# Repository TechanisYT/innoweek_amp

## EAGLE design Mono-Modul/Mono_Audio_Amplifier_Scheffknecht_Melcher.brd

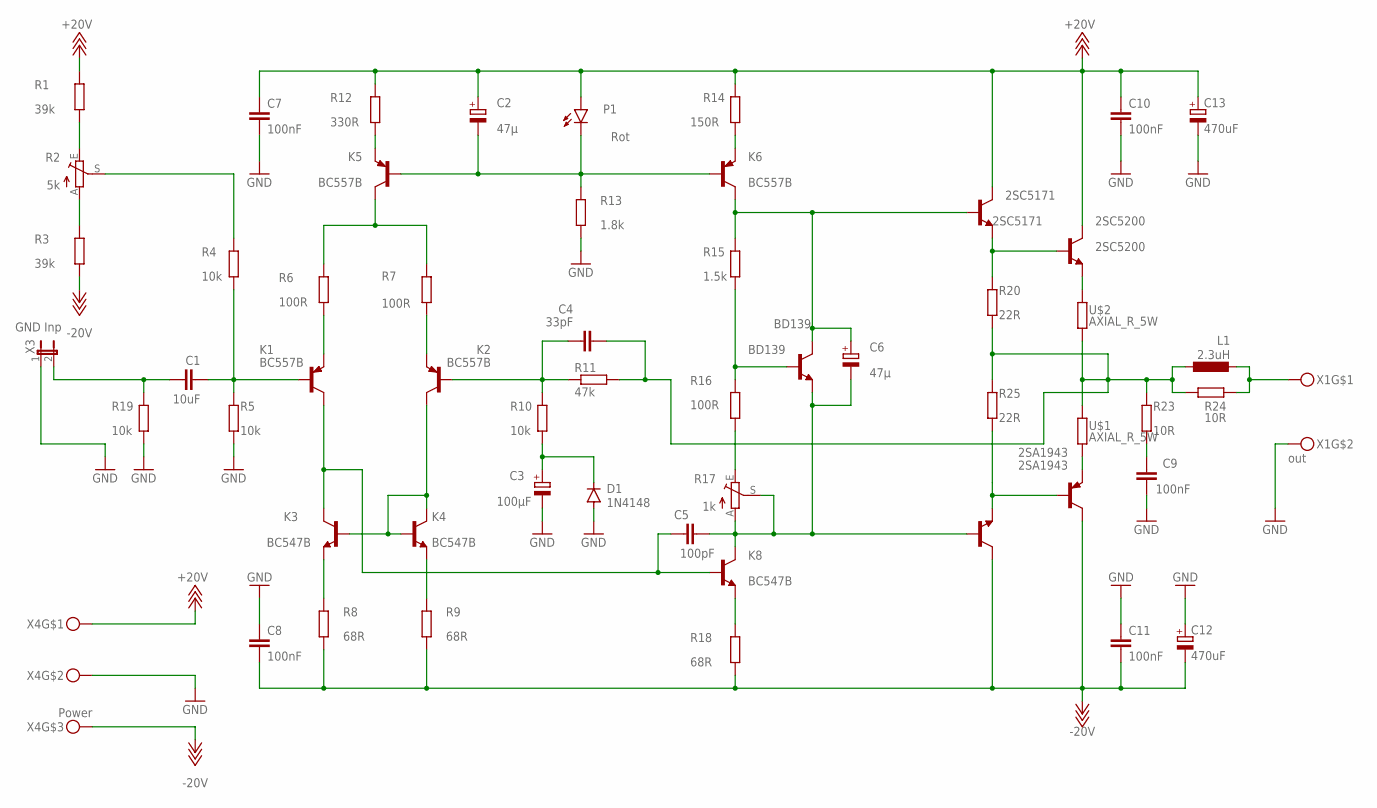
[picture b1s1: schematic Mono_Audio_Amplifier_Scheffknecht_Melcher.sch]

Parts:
2SA1930: 2SA1930; TO220BV
2SA1943: 2SA1943; TO264
2SC5171: 2SC5171; TO220BV
2SC5200: 2SC5200; TO264
BD139: BD139; TO126V
C1: 10uF; C0805
C2, C6: 47µ; E2,5-6
C3: 100µF; E2,5-7
C4: 33pF; C0805
C5: 100pF; C0805
C7, C8, C9, C10, C11: 100nF; C0805
C12, C13: 470uF; E3,5-8
D1: 1N4148; DO35-7
K1, K2, K5, K6: BC557B; TO92-EBC
K3, K4, K8: BC547B; TO92-CBE
L1: 2.3uH; TJ3-U2
P1: Rot; LED5MM
R1, R3: 39k; R0805
R2: 5k; S64W
R4, R5, R10, R19: 10k; R0805
R6, R7, R16: 100R; R0805
R8, R9, R18: 68R; R0805
R11: 47k; R0805
R12: 330R; R0805
R13: 1.8k; R0805
R14: 150R; R0805
R15: 1.5k; R0805
R17: 1k; S64W
R20, R25: 22R; R0805
R23, R24: 10R; R0805
U$1, U$2: AXIAL_R_5W; AXIAL_RESISTOR
X1: out; MKDS3/2_5,08
X3: GND Inp; JMP2
X4: Power; MKDS3/3_5,08

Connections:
+18V: 2SC5171.2 (C), 2SC5200.2 (C), C2.+, C7.1, C10.1, C13.+, P1.A, R1.1, R12.1, R14.1, X4.P$1
-18V: 2SA1930.2 (C), 2SA1943.2 (C), C8.2, C11.2, C12.-, R3.2, R8.2, R9.2, R18.2, X4.P$3
AUX_IN: C1.2, K1.B, R4.2, R5.1
GND: C3.-, C7.2, C8.1, C9.1, C10.2, C11.1, C12.+, C13.-, D1.A, R5.2, R13.2, R19.2, X1.P$2, X3.1, X4.P$2
unnamed: 2SC5200.3 (E), U$2.P$2 (2)
unnamed: 2SC5171.3 (E), 2SC5200.1 (B), R20.2
unnamed: 2SA1943.3 (E), U$1.P$1 (1)
unnamed: C4.2, L1.1, R11.2, R20.1, R23.2, R24.2, R25.2, U$1.P$2 (2), U$2.P$1 (1)
unnamed: C5.1, K1.C, K3.C, K8.B
unnamed: R16.2, R17.E
unnamed: BD139.3 (B), R15.2, R16.1
unnamed: 2SA1930.1 (B), BD139.1 (E), C5.2, C6.-, K8.C, R17.A, R17.S
unnamed: 2SC5171.1 (B), BD139.2 (C), C6.+, K6.C, R15.1
unnamed: K8.E, R18.1
unnamed: K6.E, R14.2
unnamed: K5.C, R6.1, R7.1
unnamed: K5.E, R12.2
unnamed: C4.1, K2.B, R10.1, R11.1
unnamed: K4.E, R9.1
unnamed: C2.-, K5.B, K6.B, P1.K (C), R13.1
unnamed: K1.E, R6.2
unnamed: K3.E, R8.1
unnamed: K2.E, R7.2
unnamed: K2.C, K3.B, K4.B, K4.C
unnamed: C3.+, D1.C, R10.2
unnamed: C9.2, R23.1
unnamed: C1.1, R19.1, X3.2
unnamed: R1.2, R2.E
unnamed: 2SA1930.3 (E), 2SA1943.1 (B), R25.1
unnamed: R2.S, R4.1
unnamed: R2.A, R3.1
unnamed: L1.2, R24.1, X1.P$1

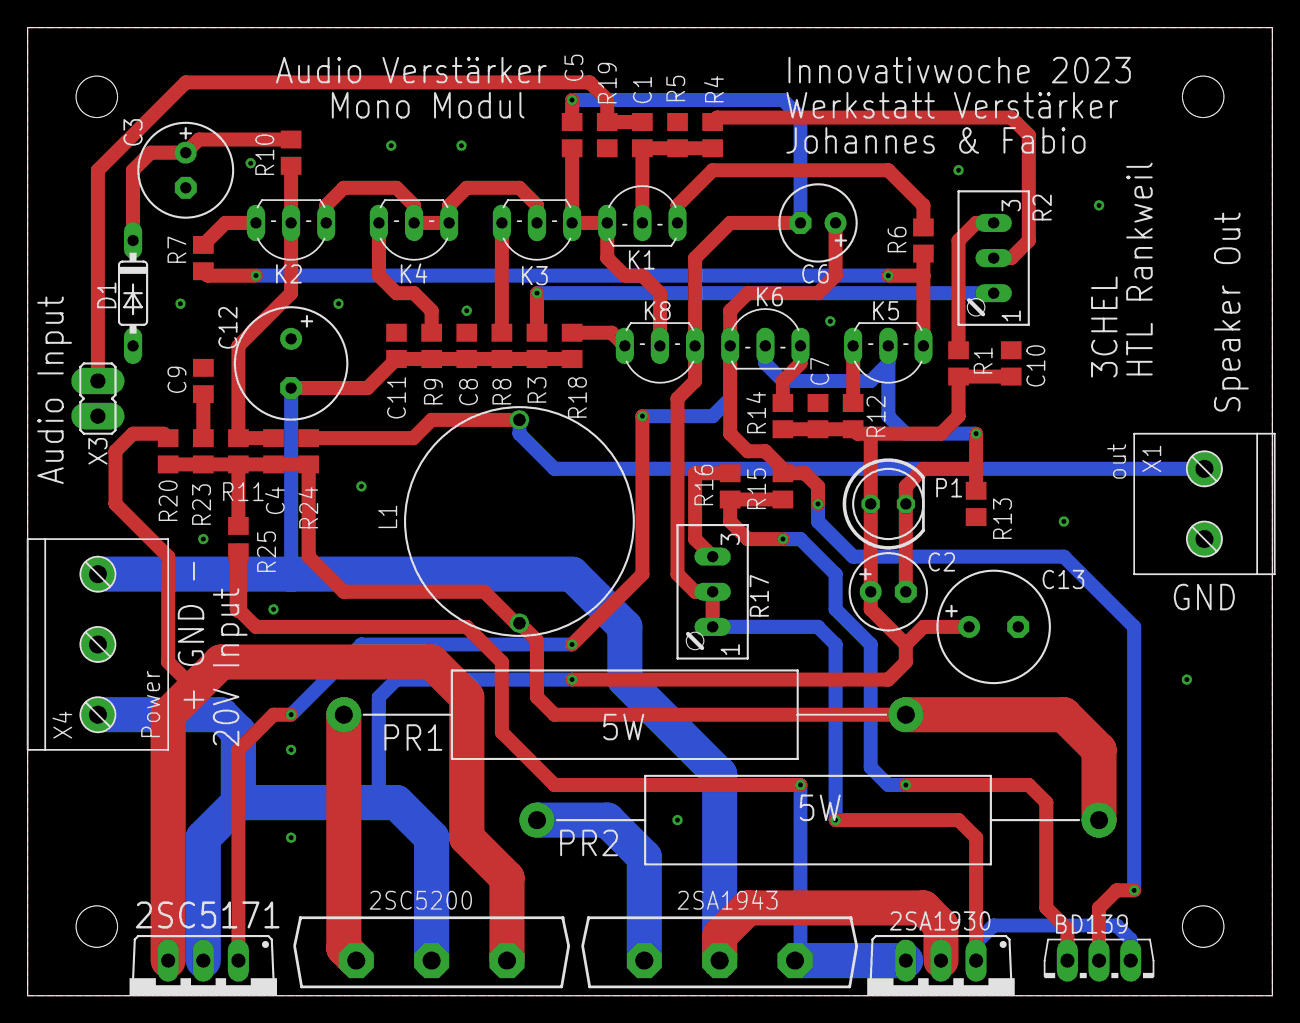
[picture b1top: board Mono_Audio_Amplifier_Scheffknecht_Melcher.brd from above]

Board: 2 copper layers, 90.0 x 70.0 mm, 56 parts (0 on the bottom side), 32 nets.

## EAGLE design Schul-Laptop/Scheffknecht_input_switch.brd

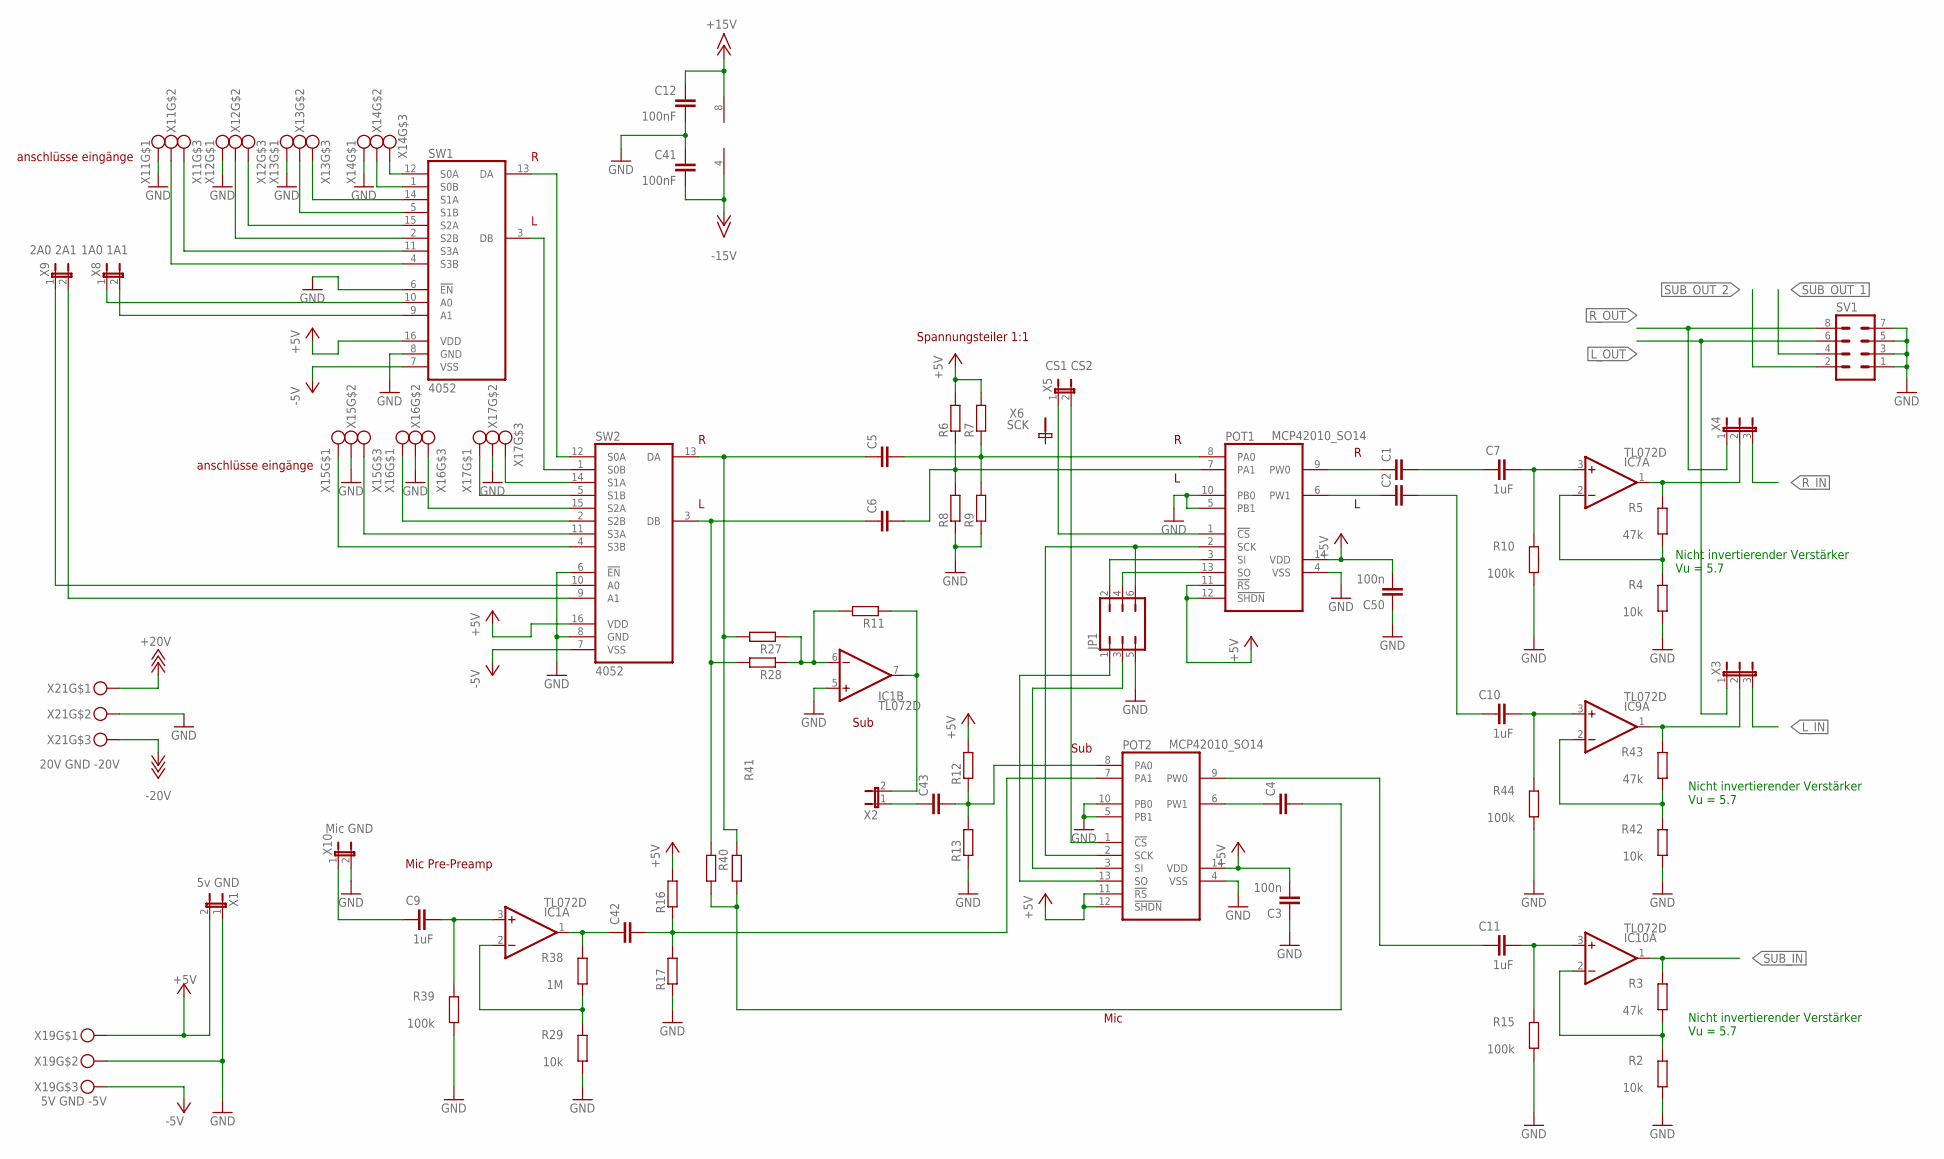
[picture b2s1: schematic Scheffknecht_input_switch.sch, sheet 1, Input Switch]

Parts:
C1, C2, C4, C5, C6, C42, C43: C-EUC0805; C0805
C3, C50: 100n; C0805
C7, C9, C10, C11: 1uF; C025-025X050
C12, C41: 100nF; C0805
FRAME1: HTL-A3-H; HTL-LEER
IC1, IC7, IC9, IC10: TL072D; SO08
JP1: JP3Q
POT1, POT2: MCP42010_SO14; SO14
R2, R4, R29, R42: 10k; M0805
R3, R5, R43: 47k; M0805
R6, R7, R8, R9, R11, R12, R13, R16, R17, R27, R28, R40, R41: R-EU_M0805; M0805
R10, R15, R39, R44: 100k; M0805
R38: 1M; M0805
SV1: MA04-2
SW1, SW2: 4052; SO-16
X1: 5v GND; JMP2
X2: JMP2
X3, X4: JMP3
X5: CS1 CS2; JMP2
X6: SCK; PIN1
X8: 1A0 1A1; JMP2
X9: 2A0 2A1; JMP2
X10: Mic GND; JMP2
X11, X12, X13, X14, X15, X16, X17: MKDS3/3_5,08
X19: 5V GND -5V; MKDS3/3_5,08
X21: 20V GND -20V; MKDS3/3_5,08

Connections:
+5V: C3.2, C50.2, POT1.11 (!RS), POT1.12 (!SHDN), POT1.14 (VDD), POT2.11 (!RS), POT2.12 (!SHDN), POT2.14 (VDD), R6.2, R7.2, R12.2, R16.2, SW1.16 (VDD), SW2.16 (VDD), X1.2, X19.P$1; also elsewhere on the board
+15V: C12.1, IC1.8 (V+); also elsewhere on the board
+18V: X21.P$1; also elsewhere on the board
-5V: SW1.7 (VSS), SW2.7 (VSS), X19.P$3; also elsewhere on the board
-15V: C41.2, IC1.4 (V-); also elsewhere on the board
-18V: X21.P$3; also elsewhere on the board
GND: C3.1, C12.2, C41.1, C50.1, IC1.5 (+IN), JP1.5, POT1.4 (VSS), POT1.5 (PB1), POT1.10 (PB0), POT2.4 (VSS), POT2.5 (PB1), POT2.10 (PB0), R2.1, R4.1, R8.1, R9.1, R10.1, R13.1, R15.1, R17.1, R29.1, R39.1, R42.1, R44.1, SV1.1, SV1.3, SV1.5, SV1.7, SW1.6 (!EN), SW1.8 (GND), SW2.6 (!EN), SW2.8 (GND), X1.1, X10.2, X11.P$1, X12.P$1, X13.P$1, X14.P$1, X15.P$2, X16.P$2, X17.P$2, X19.P$2, X21.P$2; also elsewhere on the board
L_IN: X3.3; also elsewhere on the board
L_OUT: SV1.6, X3.1; also elsewhere on the board
unnamed: POT2.1 (!CS), X5.2
unnamed: POT1.1 (!CS), X5.1
unnamed: SW1.3 (DB), SW2.1 (S0B)
unnamed: SW1.13 (DA), SW2.12 (S0A)
unnamed: SW1.9 (A1), X8.2
unnamed: SW1.10 (A0), X8.1
unnamed: SW2.9 (A1), X9.2
unnamed: SW2.10 (A0), X9.1
unnamed: C5.2, POT1.8 (PA0), R7.1, R9.2
unnamed: JP1.2, POT1.3 (SI)
unnamed: C7.2, IC7.3 (+IN), R10.2
unnamed: C5.1, R27.2, R41.1, SW2.13 (DA)
unnamed: C6.1, R28.2, R40.1, SW2.3 (DB)
unnamed: C2.2, C10.1
unnamed: C10.2, IC9.3 (+IN), R44.2
unnamed: IC1.6 (-IN), R11.2, R27.1, R28.1
unnamed: IC9.2 (-IN), R42.2, R43.1
unnamed: C1.1, POT1.9 (PW0)
unnamed: C6.2, POT1.7 (PA1), R6.1, R8.2
unnamed: C11.1, POT2.9 (PW0)
unnamed: C1.2, C7.1
unnamed: C11.2, IC10.3 (+IN), R15.2
unnamed: IC10.2 (-IN), R2.2, R3.1
unnamed: JP1.1, POT2.13 (SO)
unnamed: C2.1, POT1.6 (PW1)
unnamed: IC7.2 (-IN), R4.2, R5.1
unnamed: C43.2, POT2.8 (PA0), R12.1, R13.2
unnamed: C9.1, X10.1
unnamed: JP1.4, POT1.13 (SO)
unnamed: JP1.3, POT2.3 (SI)
unnamed: C4.1, POT2.6 (PW1)
unnamed: IC1.7 (OUT), R11.1, X2.2
unnamed: C42.2, POT2.7 (PA1), R16.1, R17.2
unnamed: JP1.6, POT1.2 (SCK), POT2.2 (SCK)
unnamed: SW1.12 (S0A), X14.P$3
unnamed: SW1.1 (S0B), X14.P$2
unnamed: SW1.14 (S1A), X13.P$3
unnamed: SW1.5 (S1B), X13.P$2
unnamed: SW1.15 (S2A), X12.P$3
unnamed: SW1.2 (S2B), X12.P$2
unnamed: SW1.11 (S3A), X11.P$3
unnamed: SW1.4 (S3B), X11.P$2
unnamed: SW2.14 (S1A), X17.P$3
unnamed: SW2.5 (S1B), X17.P$1
unnamed: SW2.15 (S2A), X16.P$3
unnamed: SW2.2 (S2B), X16.P$1
unnamed: SW2.11 (S3A), X15.P$3
unnamed: SW2.4 (S3B), X15.P$1
unnamed: C9.2, IC1.3 (+IN), R39.2
unnamed: IC9.1 (OUT), R43.2, X3.2
unnamed: IC7.1 (OUT), R5.2, X4.2
unnamed: IC1.2 (-IN), R29.2, R38.1
unnamed: C43.1, X2.1
unnamed: C42.1, IC1.1 (OUT), R38.2
unnamed: C4.2, R40.2, R41.2
R_IN: X4.3; also elsewhere on the board
R_OUT: SV1.8, X4.1; also elsewhere on the board
SUB_IN: IC10.1 (OUT), R3.2; also elsewhere on the board
SUB_OUT_1: SV1.4; also elsewhere on the board
SUB_OUT_2: SV1.2; also elsewhere on the board
V+: IC7.8 (V+), IC9.8 (V+), IC10.8 (V+)
V-: IC7.4 (V-), IC9.4 (V-), IC10.4 (V-)

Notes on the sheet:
Spannungsteiler 1:1
Sub
anschlüsse eingänge
Mic Pre-Preamp
Mic
Nicht invertierender Verstärker Vu = 5.7

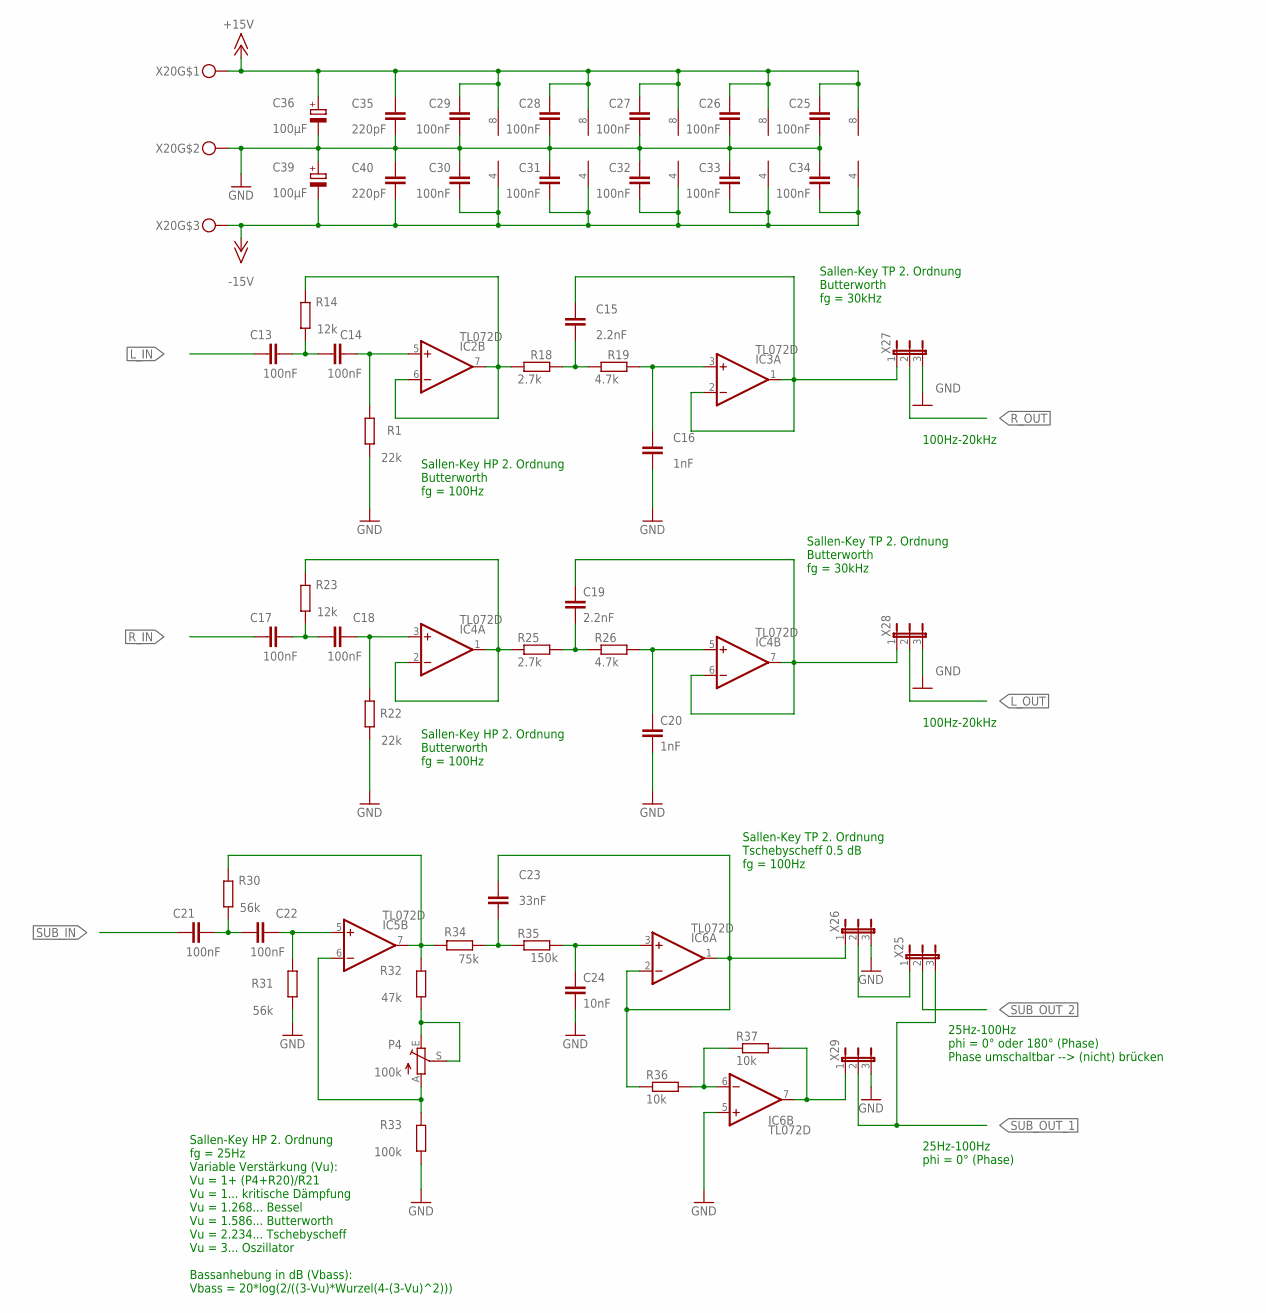
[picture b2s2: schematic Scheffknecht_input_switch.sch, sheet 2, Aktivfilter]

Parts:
C13, C14, C17, C18, C21, C22, C25, C26, C27, C28, C29, C30, C31, C32, C33, C34: 100nF; C0805
C15, C19: 2.2nF; C0805
C16, C20: 1nF; C0805
C23: 33nF; C0805
C24: 10nF; C0805
C35, C40: 220pF; C0805
C36, C39: 100µF; E2,5-6
FRAME2: HTL-A3-H; HTL-LEER
IC2, IC3, IC4, IC5, IC6: TL072D; SO08
P4: 100k; S64W
R1, R22: 22k; M0805
R14, R23: 12k; M0805
R18, R25: 2.7k; M0805
R19, R26: 4.7k; M0805
R30, R31: 56k; M0805
R32: 47k; M0805
R33: 100k; M0805
R34: 75k; M0805
R35: 150k; M0805
R36, R37: 10k; M0805
X20: MKDS3/3_5,08
X25, X26, X27, X28, X29: JMP3

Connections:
+15V: C25.1, C26.1, C27.1, C28.1, C29.1, C35.1, C36.+, IC2.8 (V+), IC3.8 (V+), IC4.8 (V+), IC5.8 (V+), IC6.8 (V+), X20.P$1; also elsewhere on the board
-15V: C30.2, C31.2, C32.2, C33.2, C34.2, C39.-, C40.2, IC2.4 (V-), IC3.4 (V-), IC4.4 (V-), IC5.4 (V-), IC6.4 (V-), X20.P$3; also elsewhere on the board
GND: C16.2, C20.2, C24.2, IC6.5 (+IN), R1.1, R22.1, R31.1, R33.1, X26.3, X27.3, X28.3, X29.3; also elsewhere on the board
GND1: C25.2, C26.2, C27.2, C28.2, C29.2, C30.1, C31.1, C32.1, C33.1, C34.1, C35.2, C36.-, C39.+, C40.1, X20.P$2
L_IN: C13.1; also elsewhere on the board
L_OUT: X28.2; also elsewhere on the board
unnamed: IC2.6 (-IN), IC2.7 (OUT), R14.2, R18.1
unnamed: C14.2, IC2.5 (+IN), R1.2
unnamed: C13.2, C14.1, R14.1
unnamed: C15.2, R18.2, R19.1
unnamed: C16.1, IC3.3 (+IN), R19.2
unnamed: C15.1, IC3.1 (OUT), IC3.2 (-IN), X27.1
unnamed: IC4.1 (OUT), IC4.2 (-IN), R23.2, R25.1
unnamed: C18.2, IC4.3 (+IN), R22.2
unnamed: C17.2, C18.1, R23.1
unnamed: C19.2, R25.2, R26.1
unnamed: C20.1, IC4.5 (+IN), R26.2
unnamed: C19.1, IC4.6 (-IN), IC4.7 (OUT)
unnamed: C21.2, C22.1, R30.1
unnamed: C22.2, IC5.5 (+IN), R31.2
unnamed: IC5.7 (OUT), R30.2, R32.2, R34.2
unnamed: IC5.6 (-IN), P4.A, R33.2
unnamed: P4.E, P4.S, R32.1
unnamed: C24.1, IC6.3 (+IN), R35.2
unnamed: C23.2, R34.1, R35.1
unnamed: IC6.6 (-IN), R36.2, R37.1
unnamed: X25.1, X26.2
R_IN: C17.1; also elsewhere on the board
R_OUT: X27.2; also elsewhere on the board
SUB_IN: C21.1; also elsewhere on the board
SUB_OUT: IC6.7 (OUT), R37.2, X29.1
SUB_OUT-180: C23.1, IC6.1 (OUT), IC6.2 (-IN), R36.1, X26.1
SUB_OUT_1: X25.3, X29.2; also elsewhere on the board
SUB_OUT_2: X25.2; also elsewhere on the board

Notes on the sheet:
100Hz-20kHz
25Hz-100Hz phi = 0° oder 180° (Phase) Phase umschaltbar --> (nicht) brücken
25Hz-100Hz phi = 0° (Phase)
Sallen-Key TP 2. Ordnung Butterworth fg = 30kHz
Sallen-Key HP 2. Ordnung Butterworth fg = 100Hz
Sallen-Key TP 2. Ordnung Tschebyscheff 0.5 dB fg = 100Hz
Sallen-Key HP 2. Ordnung fg = 25Hz Variable Verstärkung (Vu): Vu = 1+ (P4+R20)/R21 Vu = 1... kritische Dämpfung Vu = 1.268... Bessel Vu = 1.586... Butterworth Vu = 2.234... Tschebyscheff Vu = 3... Oszillator Bassanhebung in dB (Vbass): Vbass = 20*log(2/((3-Vu)*Wurzel(4-(3-Vu)^2)))

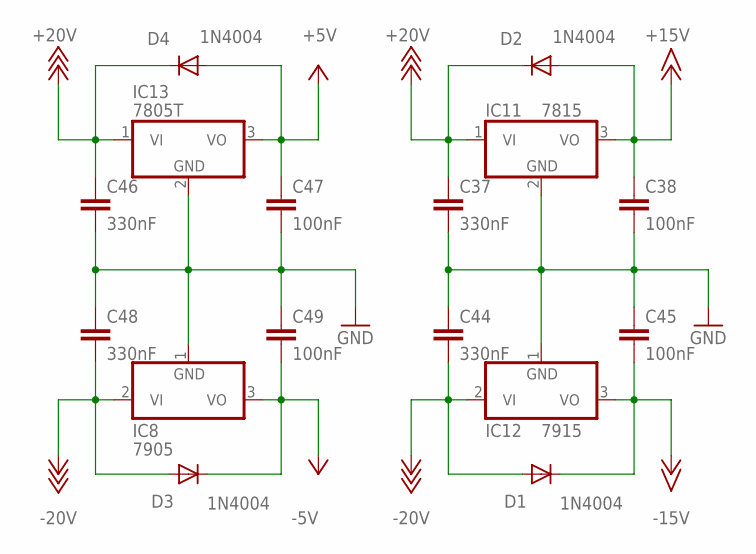
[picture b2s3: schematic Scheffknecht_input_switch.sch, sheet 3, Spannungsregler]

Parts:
C37, C44, C46, C48: 330nF; C0805
C38, C45, C47, C49: 100nF; C0805
D1, D2, D3, D4: 1N4004; DO41-10
FRAME3: HTL-A4-H; HTL-LEER
IC8: 7905; TO220H
IC11: 7815; TO220H
IC12: 7915; TO220H
IC13: 7805T; TO220H

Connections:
+5V: C47.1, D4.A, IC13.3 (VO); also elsewhere on the board
+15V: C38.1, D2.A, IC11.3 (VO); also elsewhere on the board
+18V: C37.1, C46.1, D2.C, D4.C, IC11.1 (VI), IC13.1 (VI); also elsewhere on the board
-5V: C49.2, D3.C, IC8.3 (VO); also elsewhere on the board
-15V: C45.2, D1.C, IC12.3 (VO); also elsewhere on the board
-18V: C44.2, C48.2, D1.A, D3.A, IC8.2 (VI), IC12.2 (VI); also elsewhere on the board
GND: C37.2, C38.2, C44.1, C45.1, C46.2, C47.2, C48.1, C49.1, IC8.1 (GND), IC11.2 (GND), IC12.1 (GND), IC13.2 (GND); also elsewhere on the board

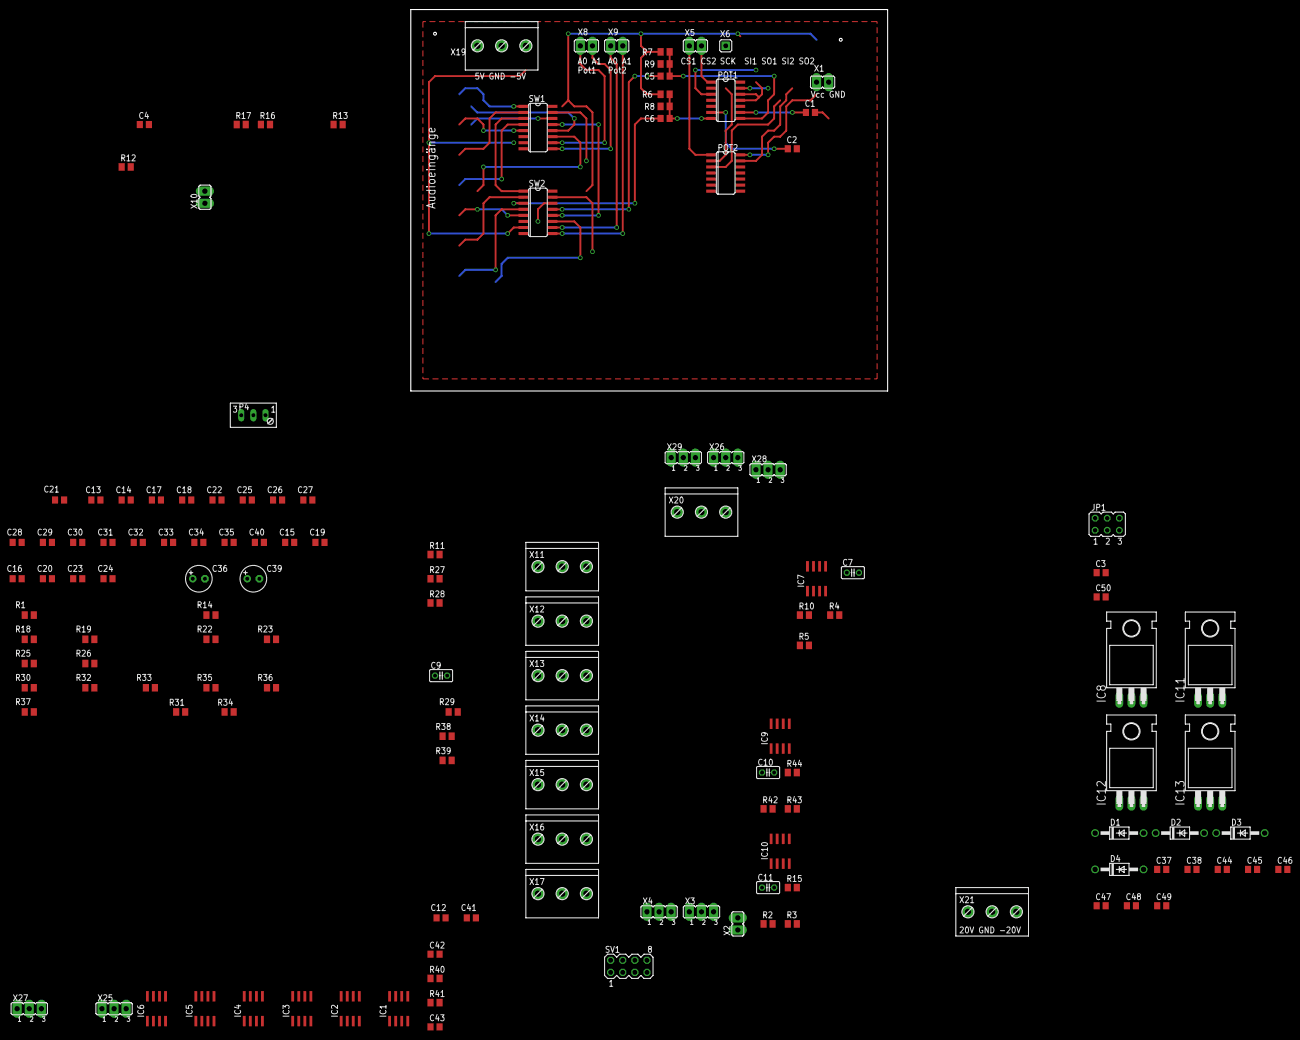
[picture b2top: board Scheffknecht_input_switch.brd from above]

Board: 2 copper layers, 100.0 x 80.0 mm, 141 parts (0 on the bottom side), 95 nets.

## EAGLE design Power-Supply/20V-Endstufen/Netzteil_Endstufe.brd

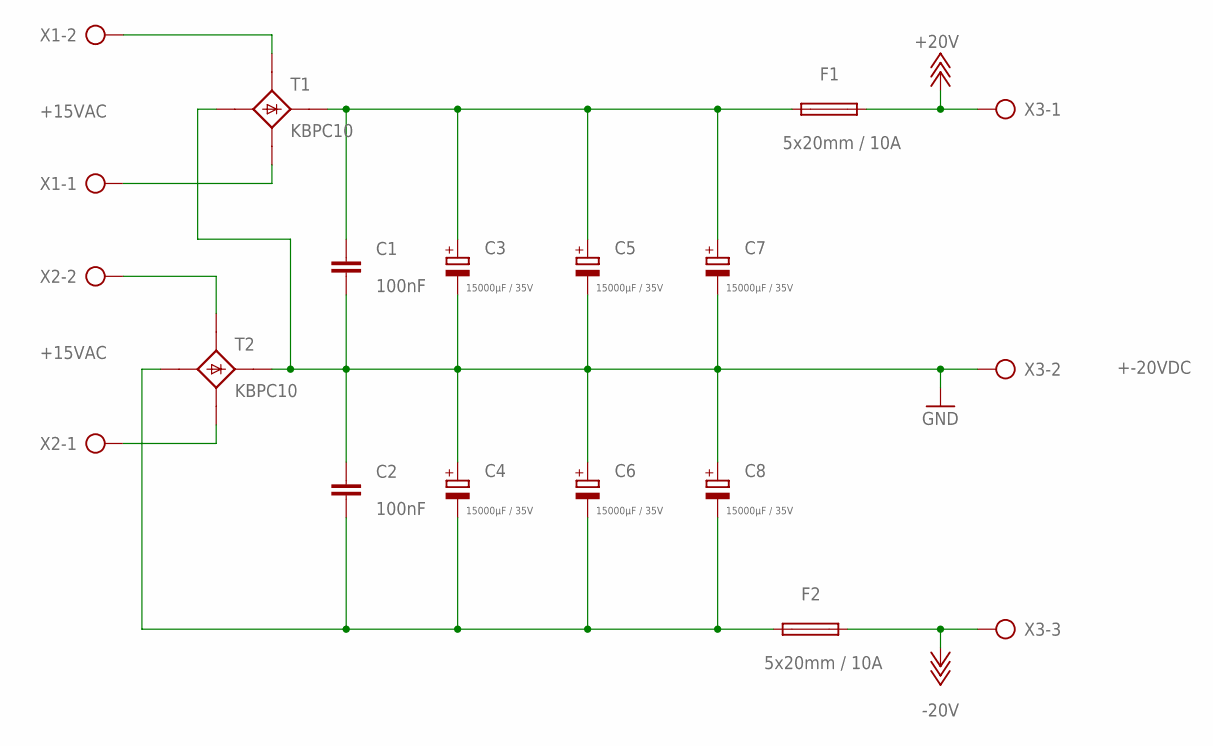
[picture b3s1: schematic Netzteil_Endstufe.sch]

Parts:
C1, C2: 100nF; C025-025X050
C3, C4, C5, C6, C7, C8: 15000µF / 35V; EB22,5D
F1, F2: 5x20mm / 10A; SHK20L
T1, T2: KBPC10; B25A-
X1, X2: +15VAC; AK300/2
X3: +-20VDC; AK300/3

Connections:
+18V: F1.2A (2), X3.1
-18V: F2.2A (2), X3.3
GND: C1.2, C2.1, C3.-, C4.+, C5.-, C6.+, C7.-, C8.+, T1.-1 (-), T2.+1 (+), X3.2
unnamed: T2.AC1- (AC1), X2.2
unnamed: C1.1, C3.+, C5.+, C7.+, F1.1A (1), T1.+1 (+)
unnamed: C2.2, C4.-, C6.-, C8.-, F2.1A (1), T2.-1 (-)
unnamed: T1.AC1- (AC1), X1.2
unnamed: T1.AC2- (AC2), X1.1
unnamed: T2.AC2- (AC2), X2.1

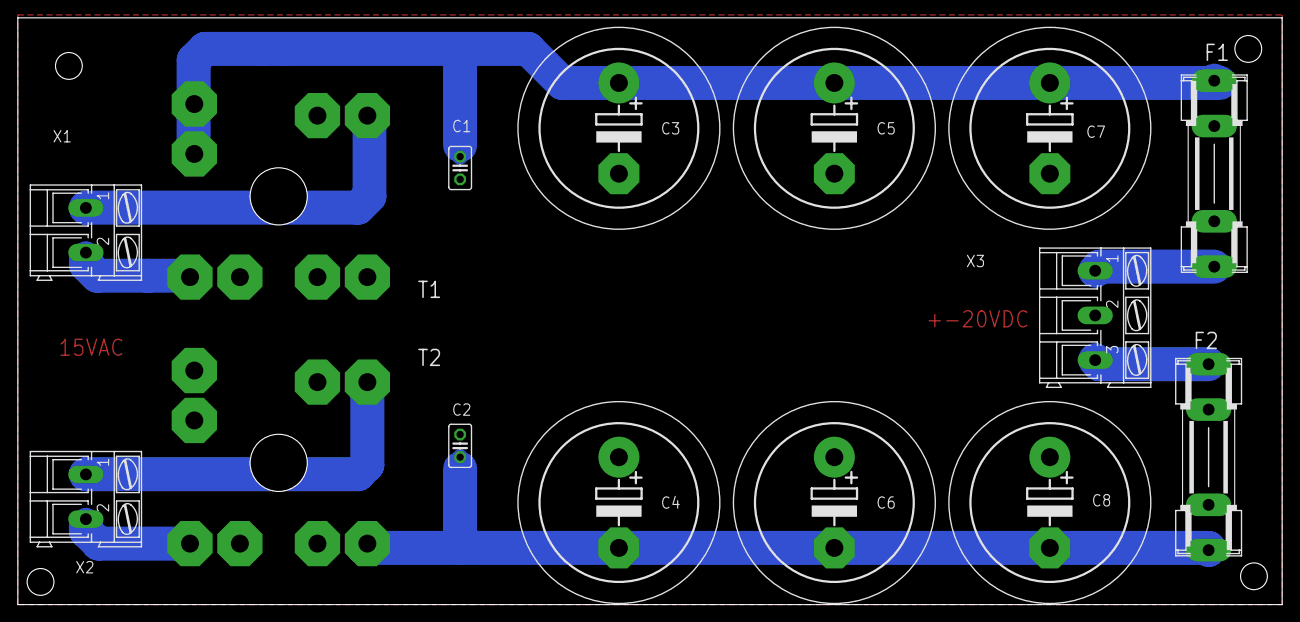
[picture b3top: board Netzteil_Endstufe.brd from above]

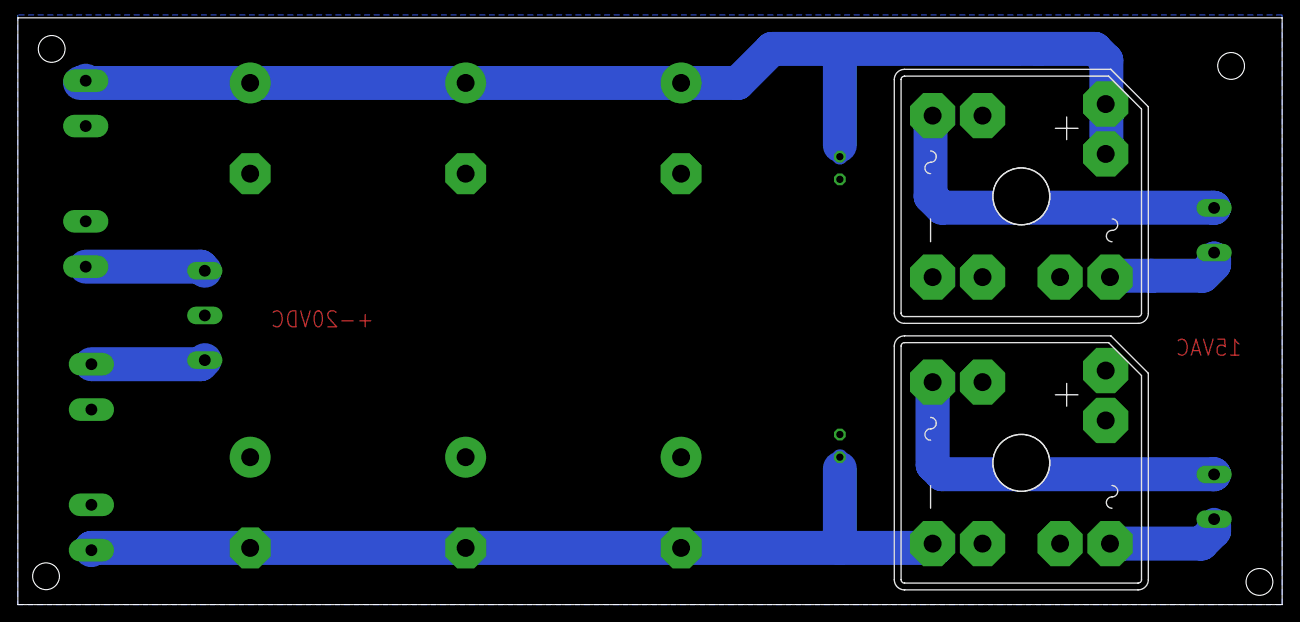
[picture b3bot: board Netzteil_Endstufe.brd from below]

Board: 2 copper layers, 141.6 x 65.7 mm, 15 parts (2 on the bottom side), 9 nets.

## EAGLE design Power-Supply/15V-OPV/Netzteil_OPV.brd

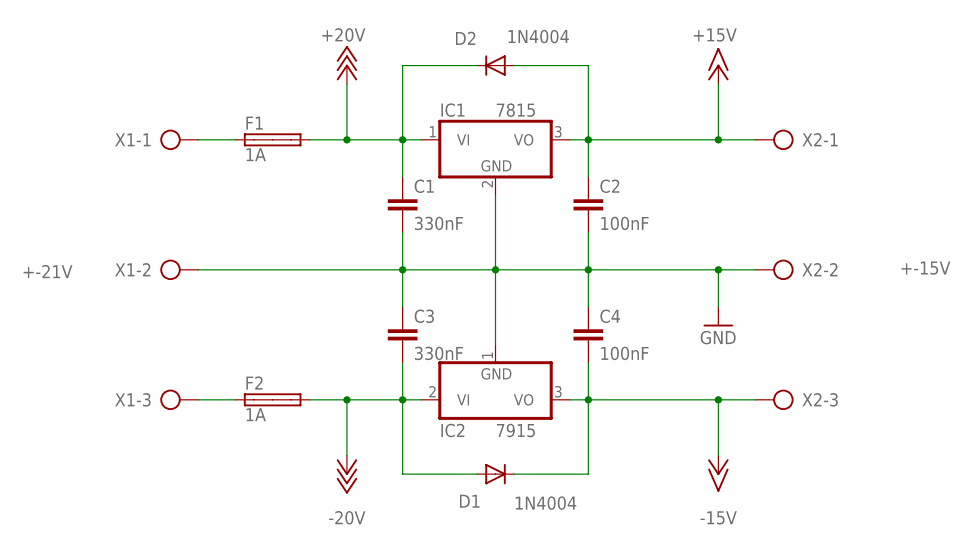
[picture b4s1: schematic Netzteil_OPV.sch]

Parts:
C1, C3: 330nF; C025-025X050
C2, C4: 100nF; C025-025X050
D1, D2: 1N4004; DO41-10
F1, F2: 1A; SHK20L
IC1: 7815; TO220H
IC2: 7915; TO220H
X1: +-21V; AK300/3
X2: +-15V; AK300/3

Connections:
+15V: C2.1, D2.A, IC1.3 (VO), X2.1
+18V: C1.1, D2.C, F1.2A, IC1.1 (VI)
-15V: C4.2, D1.C, IC2.3 (VO), X2.3
-18V: C3.2, D1.A, F2.2A, IC2.2 (VI)
GND: C1.2, C2.2, C3.1, C4.1, IC1.2 (GND), IC2.1 (GND), X1.2, X2.2
unnamed: F1.1A, X1.1
unnamed: F2.1A, X1.3

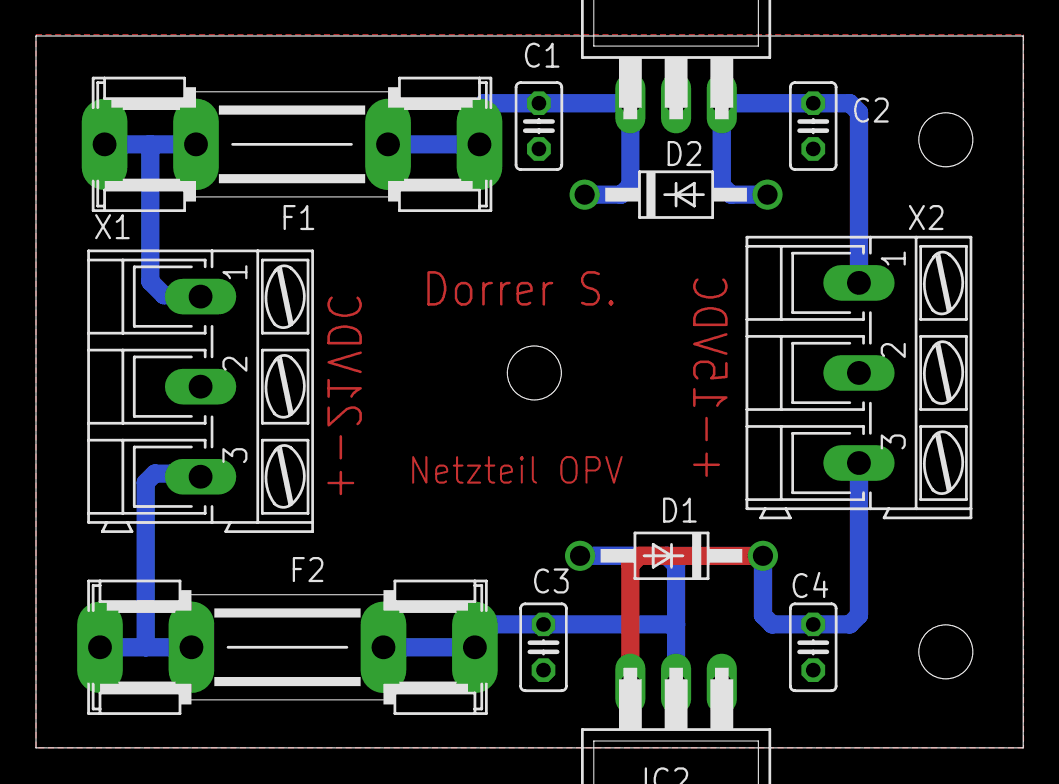
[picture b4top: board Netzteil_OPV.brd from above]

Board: 2 copper layers, 54.8 x 39.5 mm, 12 parts (0 on the bottom side), 7 nets.

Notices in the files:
parts and their libraries:
SparkFun-Connectors: Licensing: Creative Commons ShareAlike 4.0 International - https://creativecommons.org/licenses/by-sa/4.0
